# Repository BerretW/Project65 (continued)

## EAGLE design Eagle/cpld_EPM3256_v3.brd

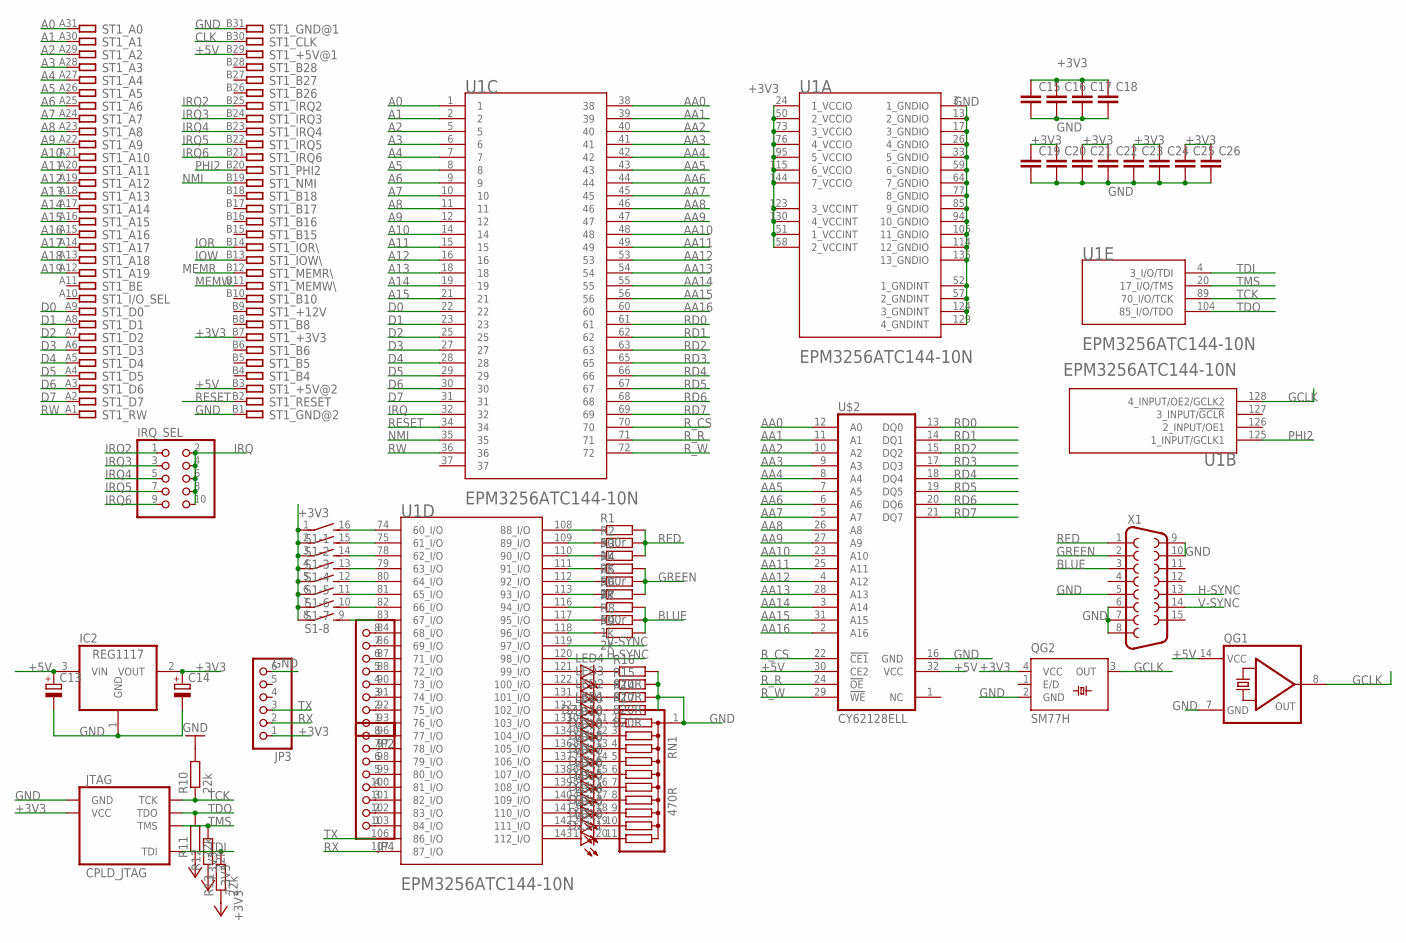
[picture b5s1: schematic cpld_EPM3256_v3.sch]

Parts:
C13, C14: CPOL-EUE2.5-5; E2,5-5
C15, C16, C17, C18, C19, C20, C21, C22, C23, C24, C25, C26: C-EU050-035X075; C050-035X075
DZ1: LB10
IC2: REG1117; SOT223
IRQ_SEL: PINHD-2X5; 2X05
JP2, JP4: PINHD-1X8; 1X08
JP3: PINHD-1X6/90; 1X06/90
JTAG: CPLD_JTAG; 2X05
LED1, LED2, LED3, LED4: LED3MM
QG1: QG5860; DIL14S
QG2: SM77H
R1, R4, R7: 500r; 0204V
R2, R5, R8: 1k; 0204V
R3, R6, R9: 2k; 0204V
R10, R11, R12, R13: 22k; 0207/7
R14, R15, R16, R17: 820R; 0207/2V
RN1: 470R; SIL11
S1: DIP08S
ST1: IBM8BIT_ISA; IBM8BIT
U1: EPM3256ATC144; TQFP144-BB
U$2: CY62128ELL; SOIC32
X1: F15HDH; HDF15H

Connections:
74: S1.16 (2), U1.74 (60_I/O)
75: S1.15 (2), U1.75 (61_I/O)
78: S1.14 (2), U1.78 (62_I/O)
79: S1.13 (2), U1.79 (63_I/O)
80: S1.12 (2), U1.80 (64_I/O)
81: S1.11 (2), U1.81 (65_I/O)
82: S1.10 (2), U1.82 (66_I/O)
83: S1.9 (2), U1.83 (67_I/O)
84: JP2.8, U1.84 (68_I/O)
86: JP2.7, U1.86 (69_I/O)
87: JP2.6, U1.87 (71_I/O)
88: JP2.5, U1.88 (72_I/O)
90: JP2.4, U1.90 (73_I/O)
91: JP2.3, U1.91 (74_I/O)
92: JP2.2, U1.92 (75_I/O)
93: JP2.1, U1.93 (76_I/O)
96: JP4.8, U1.96 (77_I/O)
97: JP4.7, U1.97 (78_I/O)
98: JP4.6, U1.98 (79_I/O)
99: JP4.5, U1.99 (80_I/O)
100: JP4.4, U1.100 (81_I/O)
101: JP4.3, U1.101 (82_I/O)
102: JP4.2, U1.102 (83_I/O)
103: JP4.1, U1.103 (84_I/O)
121: LED4.A, U1.121 (99_I/O)
122: LED3.A, U1.122 (100_I/O)
131: LED2.A, U1.131 (101_I/O)
132: LED1.A, U1.132 (102_I/O)
133: DZ1.10 (A), U1.133 (103_I/O)
134: DZ1.9 (A), U1.134 (104_I/O)
136: DZ1.8 (A), U1.136 (105_I/O)
137: DZ1.7 (A), U1.137 (106_I/O)
138: DZ1.6 (A), U1.138 (107_I/O)
139: DZ1.5 (A), U1.139 (108_I/O)
140: DZ1.4 (A), U1.140 (109_I/O)
141: DZ1.3 (A), U1.141 (110_I/O)
142: DZ1.2 (A), U1.142 (111_I/O)
143: DZ1.1 (A), U1.143 (112_I/O)
+3V3: C14.+, C15.1, C16.1, C17.1, C18.1, C19.1, C20.1, C21.1, C22.1, C23.1, C24.1, C25.1, C26.1, IC2.2 (VOUT), JP3.1, JTAG.4 (VCC), QG2.4 (VCC), R11.1, R12.1, R13.1, S1.1, S1.2 (1), S1.3 (1), S1.4 (1), S1.5 (1), S1.6 (1), S1.7 (1), S1.8 (1), ST1.B7, U1.24 (1_VCCIO), U1.50 (2_VCCIO), U1.51 (1_VCCINT), U1.58 (2_VCCINT), U1.73 (3_VCCIO), U1.76 (4_VCCIO), U1.95 (5_VCCIO), U1.115 (6_VCCIO), U1.123 (3_VCCINT), U1.130 (4_VCCINT), U1.144 (7_VCCIO)
+5V: C13.+, IC2.3 (VIN), QG1.14 (VCC), ST1.B3, ST1.B29, U$2.30 (CE2), U$2.32 (VCC)
A0: ST1.A31, U1.1
A1: ST1.A30, U1.2
A2: ST1.A29, U1.5
A3: ST1.A28, U1.6
A4: ST1.A27, U1.7
A5: ST1.A26, U1.8
A6: ST1.A25, U1.9
A7: ST1.A24, U1.10
A8: ST1.A23, U1.11
A9: ST1.A22, U1.12
A10: ST1.A21, U1.14
A11: ST1.A20, U1.15
A12: ST1.A19, U1.16
A13: ST1.A18, U1.18
A14: ST1.A17, U1.19
A15: ST1.A16, U1.21
A16: ST1.A15
A17: ST1.A14
A18: ST1.A13
A19: ST1.A12
AA0: U1.38, U$2.12 (A0)
AA1: U1.39, U$2.11 (A1)
AA2: U1.40, U$2.10 (A2)
AA3: U1.41, U$2.9 (A3)
AA4: U1.42, U$2.8 (A4)
AA5: U1.43, U$2.7 (A5)
AA6: U1.44, U$2.6 (A6)
AA7: U1.45, U$2.5 (A7)
AA8: U1.46, U$2.26 (A8)
AA9: U1.47, U$2.27 (A9)
AA10: U1.48, U$2.23 (A10)
AA11: U1.49, U$2.25 (A11)
AA12: U1.53, U$2.4 (A12)
AA13: U1.54, U$2.28 (A13)
AA14: U1.55, U$2.3 (A14)
AA15: U1.56, U$2.31 (A15)
AA16: U1.60, U$2.2 (A16)
B1: R8.1, U1.117 (95_I/O)
B2: R9.1, U1.118 (96_I/O)
B5: R7.1, U1.116 (94_I/O)
BLUE: R7.2, R8.2, R9.2, X1.3
CLK: ST1.B30
D0: ST1.A9, U1.22
D1: ST1.A8, U1.23
D2: ST1.A7, U1.25
D3: ST1.A6, U1.27
D4: ST1.A5, U1.28
D5: ST1.A4, U1.29
D6: ST1.A3, U1.30
D7: ST1.A2, U1.31
G1: R5.1, U1.112 (92_I/O)
G2: R6.1, U1.113 (93_I/O)
G5: R4.1, U1.111 (91_I/O)
GCLK: QG1.8 (OUT), QG2.3 (OUT), U1.128 (4_INPUT/OE2/GCLK2)
GND: C13.-, C14.-, C15.2, C16.2, C17.2, C18.2, C19.2, C20.2, C21.2, C22.2, C23.2, C24.2, C25.2, C26.2, IC2.1 (GND), JP3.6, JTAG.2 (GND), JTAG.6 (GND), JTAG.7 (GND), JTAG.8 (GND), JTAG.10 (GND), QG1.7 (GND), QG2.2 (GND), R10.2, R14.2, R15.2, R16.2, R17.2, RN1.1, ST1.B1, ST1.B31, U1.3 (1_GNDIO), U1.13 (2_GNDIO), U1.17 (3_GNDIO), U1.26 (4_GNDIO), U1.33 (5_GNDIO), U1.52 (1_GNDINT), U1.57 (2_GNDINT), U1.59 (6_GNDIO), U1.64 (7_GNDIO), U1.77 (8_GNDIO), U1.85 (9_GNDIO), U1.94 (10_GNDIO), U1.105 (11_GNDIO), U1.114 (12_GNDIO), U1.124 (3_GNDINT), U1.129 (4_GNDINT), U1.135 (13_GNDIO), U$2.16 (GND), X1.5, X1.6, X1.7, X1.8, X1.9, X1.10
GREEN: R4.2, R5.2, R6.2, X1.2
H-SYNC: U1.120 (98_I/O), X1.13
IOR: ST1.B14
IOW: ST1.B13
IRQ: IRQ_SEL.2, IRQ_SEL.4, IRQ_SEL.6, IRQ_SEL.8, IRQ_SEL.10, U1.32
IRQ2: IRQ_SEL.1, ST1.B25
IRQ3: IRQ_SEL.3, ST1.B24
IRQ4: IRQ_SEL.5, ST1.B23
IRQ5: IRQ_SEL.7, ST1.B22
IRQ6: IRQ_SEL.9, ST1.B21
MEMR: ST1.B12
MEMW: ST1.B11
unnamed: LED2.K (C), R14.1
unnamed: LED3.K (C), R15.1
unnamed: LED4.K (C), R16.1
unnamed: LED1.K (C), R17.1
unnamed: DZ1.20 (C), RN1.11
unnamed: DZ1.19 (C), RN1.10
unnamed: DZ1.18 (C), RN1.9
unnamed: DZ1.17 (C), RN1.8
unnamed: DZ1.16 (C), RN1.7
unnamed: DZ1.15 (C), RN1.6
unnamed: DZ1.14 (C), RN1.5
unnamed: DZ1.13 (C), RN1.4
unnamed: DZ1.12 (C), RN1.3
unnamed: DZ1.11 (C), RN1.2
NMI: ST1.B19, U1.35
PHI2: ST1.B20, U1.125 (1_INPUT/GCLK1)
R1: R2.1, U1.109 (89_I/O)
R2: R3.1, U1.110 (90_I/O)
R5: R1.1, U1.108 (88_I/O)
RD0: U1.61, U$2.13 (DQ0)
RD1: U1.62, U$2.14 (DQ1)
RD2: U1.63, U$2.15 (DQ2)
RD3: U1.65, U$2.17 (DQ3)
RD4: U1.66, U$2.18 (DQ4)
RD5: U1.67, U$2.19 (DQ5)
RD6: U1.68, U$2.20 (DQ6)
RD7: U1.69, U$2.21 (DQ7)
RED: R1.2, R2.2, R3.2, X1.1
RESET: ST1.B2, U1.34
RW: ST1.A1, U1.36
RX: JP3.2, U1.107 (87_I/O)
R_CS: U1.70, U$2.22 (!CE1)
R_R: U1.71, U$2.24 (!OE)
R_W: U1.72, U$2.29 (!WE)
TCK: JTAG.1 (TCK), R10.1, U1.89 (70_I/O/TCK)
TDI: JTAG.9 (TDI), R13.2, U1.4 (3_I/O/TDI)
TDO: JTAG.3 (TDO), R11.2, U1.104 (85_I/O/TDO)
TMS: JTAG.5 (TMS), R12.2, U1.20 (17_I/O/TMS)
TX: JP3.3, U1.106 (86_I/O)
V-SYNC: U1.119 (97_I/O), X1.14

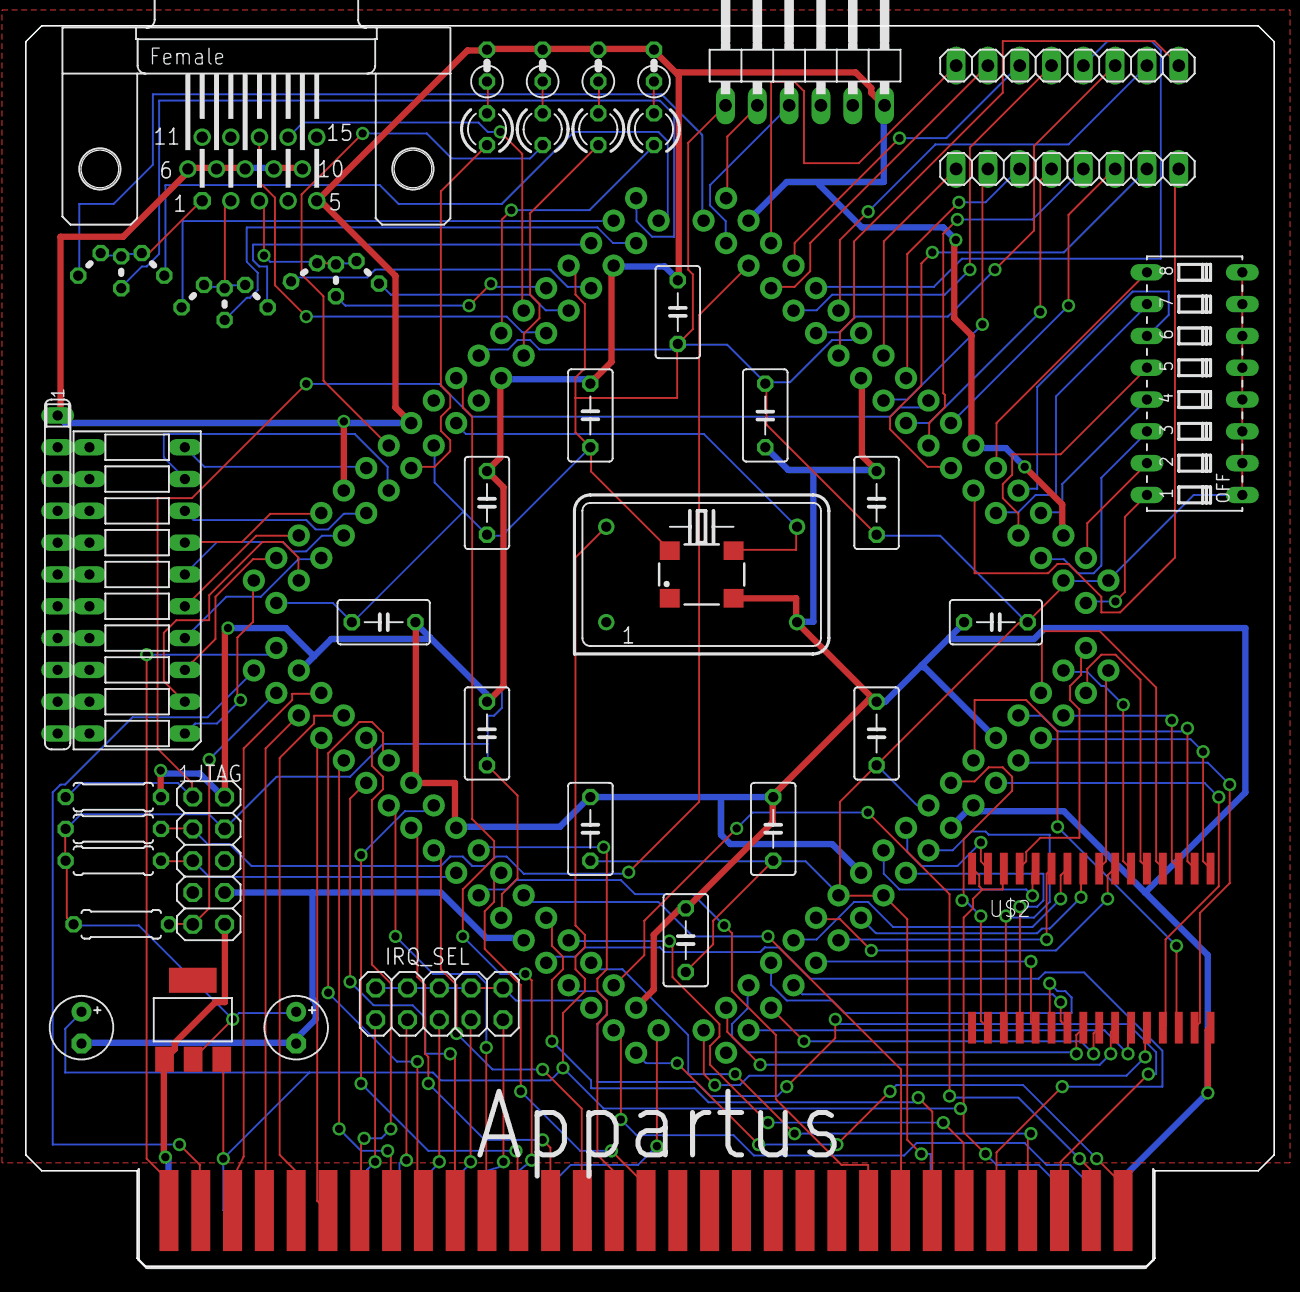
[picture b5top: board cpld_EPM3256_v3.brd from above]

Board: 2 copper layers, 99.7 x 99.1 mm, 50 parts (0 on the bottom side), 138 nets.

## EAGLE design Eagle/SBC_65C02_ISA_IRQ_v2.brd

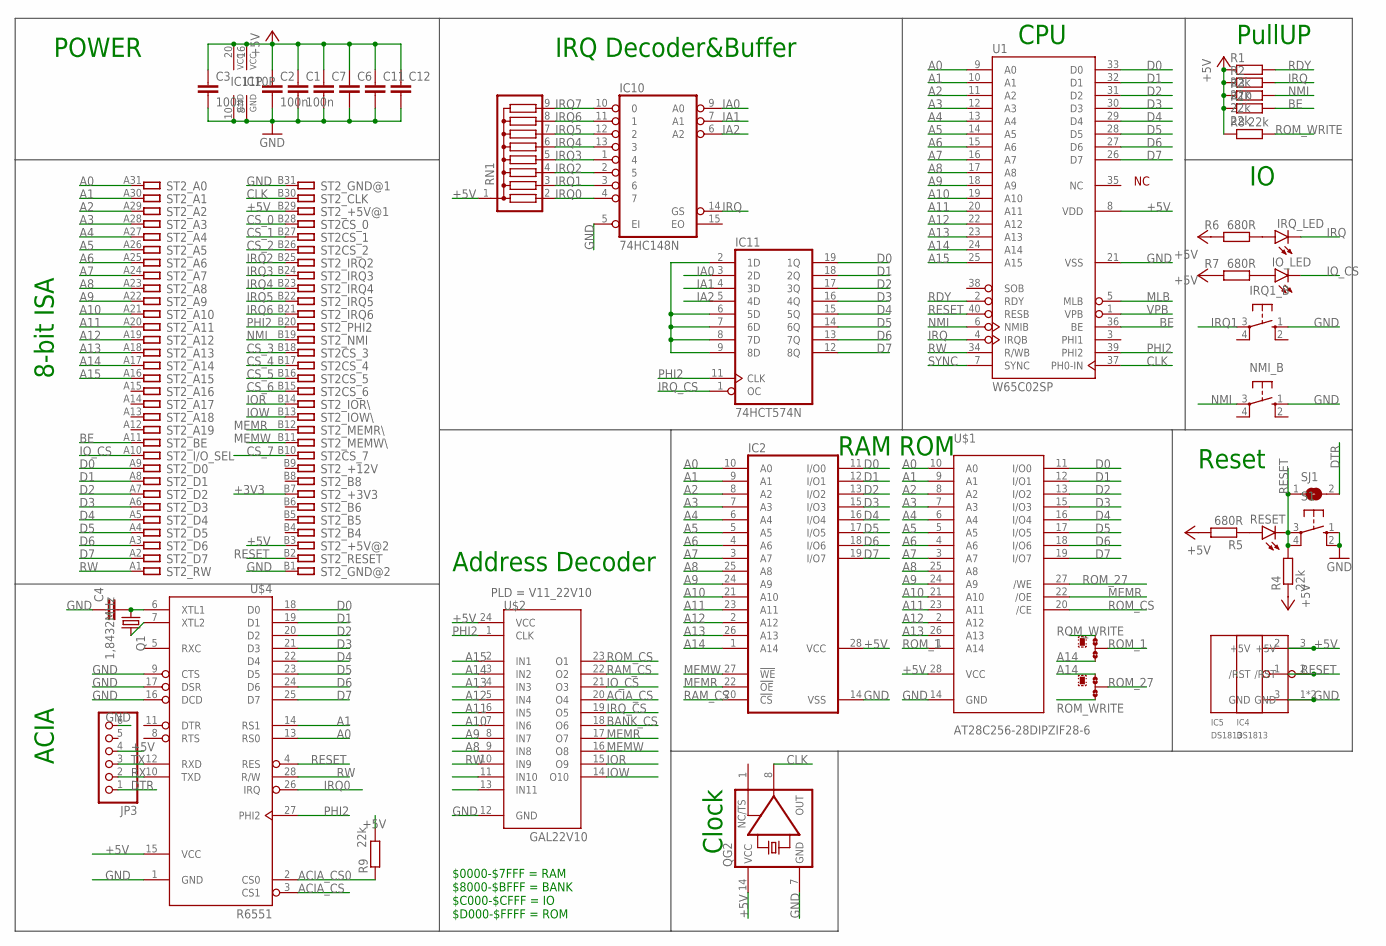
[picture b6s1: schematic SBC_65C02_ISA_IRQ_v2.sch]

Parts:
C1, C2, C3: 100n; C050-025X075
C4: C-EU025-030X050; C025-030X050
C6, C7, C11, C12: C-EU050-035X075; C050-035X075
IC2: 62256P; DIL28-6
IC4: DS1813; SOT223
IC5: DS1813; TO-92
IC10: 74HC148N; DIL16
IC11: 74HCT574N; DIL20
IO_LED: LED5MM
IRQ1_B: 10-XX; B3F-10XX
IRQ_LED: LED5MM
JP3: PINHD-1X6/90; 1X06/90
NMI_B: 10-XX; B3F-10XX
Q1: 1,8432MHz; HC49/S
QG2: XO-14; DIL14S
R1, R2, R3, R4, R8, R9, R10: 22k; 0207/10
R5, R6, R7: 680R; 0207/10
RESET: LED5MM
RN1: G08R; SIL9
ROM_1, ROM_27: 0R-JUMPA; A0R-JMP
S1: 10-XX; B3F-10XX
SJ1: SJ
ST2: IBM8BIT_ISASHORT; APP_2X32_SHORT
U1: W65C02SP; DIP-40
U$1: AT28C256-28DIPZIF28-6; 228-1277-00-0602J
U$2: GAL22V10; DIL28_1
U$4: R6551; DIP-28

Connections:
+3V3: ST2.B7
+5V: C1.1, C2.1, C3.1, C6.1, C7.1, C11.1, C12.1, IC2.28 (VCC), IC4.3 (+5V), IC5.2 (+5V), IC10.16 (VCC), IC11.20 (VCC), JP3.4, QG2.14 (VCC), R1.1, R2.1, R3.1, R4.1, R5.2, R6.2, R7.2, R8.1, R9.2, R10.1, RN1.1, ST2.B3, ST2.B29, U1.8 (VDD), U$1.28 (VCC), U$2.24 (VCC), U$4.15 (VCC)
A0: IC2.10 (A0), ST2.A31, U1.9 (A0), U$1.10 (A0), U$4.13 (RS0)
A1: IC2.9 (A1), ST2.A30, U1.10 (A1), U$1.9 (A1), U$4.14 (RS1)
A2: IC2.8 (A2), ST2.A29, U1.11 (A2), U$1.8 (A2)
A3: IC2.7 (A3), ST2.A28, U1.12 (A3), U$1.7 (A3)
A4: IC2.6 (A4), ST2.A27, U1.13 (A4), U$1.6 (A4)
A5: IC2.5 (A5), ST2.A26, U1.14 (A5), U$1.5 (A5)
A6: IC2.4 (A6), ST2.A25, U1.15 (A6), U$1.4 (A6)
A7: IC2.3 (A7), ST2.A24, U1.16 (A7), U$1.3 (A7)
A8: IC2.25 (A8), ST2.A23, U1.17 (A8), U$1.25 (A8), U$2.9 (IN8)
A9: IC2.24 (A9), ST2.A22, U1.18 (A9), U$1.24 (A9), U$2.8 (IN7)
A10: IC2.21 (A10), ST2.A21, U1.19 (A10), U$1.21 (A10), U$2.7 (IN6)
A11: IC2.23 (A11), ST2.A20, U1.20 (A11), U$1.23 (A11), U$2.6 (IN5)
A12: IC2.2 (A12), ST2.A19, U1.22 (A12), U$1.2 (A12), U$2.5 (IN4)
A13: IC2.26 (A13), ST2.A18, U1.23 (A13), U$1.26 (A13), U$2.4 (IN3)
A14: IC2.1 (A14), ROM_1.3, ROM_27.1, ST2.A17, U1.24 (A14), U$2.3 (IN2)
A15: ST2.A16, U1.25 (A15), U$2.2 (IN1)
ACIA_CS: U$2.20 (O4), U$4.3 (CS1)
ACIA_CS0: R9.1, U$4.2 (CS0)
BANK_CS: U$2.18 (O6)
BE: R10.2, ST2.A11, U1.36 (BE)
CLK: QG2.8 (OUT), ST2.B30, U1.37 (PH0-IN)
CS_0: ST2.B28
CS_1: ST2.B27
CS_2: ST2.B26
CS_3: ST2.B18
CS_4: ST2.B17
CS_5: ST2.B16
CS_6: ST2.B15
CS_7: ST2.B10
D0: IC2.11 (I/O0), IC11.19 (1Q), ST2.A9, U1.33 (D0), U$1.11 (I/O0), U$4.18 (D0)
D1: IC2.12 (I/O1), IC11.18 (2Q), ST2.A8, U1.32 (D1), U$1.12 (I/O1), U$4.19 (D1)
D2: IC2.13 (I/O2), IC11.17 (3Q), ST2.A7, U1.31 (D2), U$1.13 (I/O2), U$4.20 (D2)
D3: IC2.15 (I/O3), IC11.16 (4Q), ST2.A6, U1.30 (D3), U$1.15 (I/O3), U$4.21 (D3)
D4: IC2.16 (I/O4), IC11.15 (5Q), ST2.A5, U1.29 (D4), U$1.16 (I/O4), U$4.22 (D4)
D5: IC2.17 (I/O5), IC11.14 (6Q), ST2.A4, U1.28 (D5), U$1.17 (I/O5), U$4.23 (D5)
D6: IC2.18 (I/O6), IC11.13 (7Q), ST2.A3, U1.27 (D6), U$1.18 (I/O6), U$4.24 (D6)
D7: IC2.19 (I/O7), IC11.12 (8Q), ST2.A2, U1.26 (D7), U$1.19 (I/O7), U$4.25 (D7)
DTR: JP3.1, SJ1.2
GND: C1.2, C2.2, C3.2, C4.1, C6.2, C7.2, C11.2, C12.2, IC2.14 (VSS), IC4.1 (GND), IC4.4 (GND), IC5.3 (GND), IC10.5 (EI), IC10.8 (GND), IC11.10 (GND), IRQ1_B.1 (S), JP3.6, NMI_B.1 (S), QG2.7 (GND), S1.1 (S), S1.2 (S1), ST2.B1, ST2.B31, U1.21 (VSS), U$1.14 (GND), U$2.12 (GND), U$4.1 (GND), U$4.9 (CTS), U$4.16 (DCD), U$4.17 (DSR)
IA0: IC10.9 (A0), IC11.3 (2D)
IA1: IC10.7 (A1), IC11.4 (3D)
IA2: IC10.6 (A2), IC11.5 (4D)
IOR: ST2.B14, U$2.15 (O9)
IOW: ST2.B13, U$2.14 (O10)
IO_CS: IO_LED.K (C), ST2.A10, U$2.21 (O3)
IRQ: IC10.14 (GS), IRQ_LED.K (C), R2.2, U1.4 (IRQB)
IRQ0: IC10.4 (7), RN1.2, U$4.26 (IRQ)
IRQ1: IC10.3 (6), IRQ1_B.3, RN1.3
IRQ2: IC10.2 (5), RN1.4, ST2.B25
IRQ3: IC10.1 (4), RN1.5, ST2.B24
IRQ4: IC10.13 (3), RN1.6, ST2.B23
IRQ5: IC10.12 (2), RN1.7, ST2.B22
IRQ6: IC10.11 (1), RN1.8, ST2.B21
IRQ7: IC10.10 (0), RN1.9
IRQ_CS: IC11.1 (OC), U$2.19 (O5)
MEMR: IC2.22 (!OE), ST2.B12, U$1.22 (/OE), U$2.17 (O7)
MEMW: IC2.27 (!WE), ST2.B11, U$2.16 (O8)
MLB: U1.5 (MLB)
unnamed: IRQ_LED.A, R6.1
unnamed: R5.1, RESET.A
unnamed: IO_LED.A, R7.1
unnamed: IC11.2 (1D), IC11.6 (5D), IC11.7 (6D), IC11.8 (7D), IC11.9 (8D)
unnamed: C4.2, Q1.1, U$4.6 (XTL1)
unnamed: Q1.2, U$4.7 (XTL2)
NMI: NMI_B.3, R3.2, ST2.B19, U1.6 (NMIB)
PHI2: IC11.11 (CLK), ST2.B20, U1.39 (PHI2), U$2.1 (CLK), U$4.27 (PHI2)
RAM_CS: IC2.20 (!CS), U$2.22 (O2)
RDY: R1.2, U1.2 (RDY)
RESET: IC4.2 (/RST), IC5.1 (/RST), R4.2, RESET.K (C), S1.3, S1.4 (P1), SJ1.1, ST2.B2, U1.40 (RESB), U$4.4 (RES)
ROM_1: ROM_1.2, U$1.1 (A14)
ROM_27: ROM_27.2, U$1.27 (/WE)
ROM_CS: U$1.20 (/CE), U$2.23 (O1)
ROM_WRITE: R8.2, ROM_1.1, ROM_27.3
RW: ST2.A1, U1.34 (R/WB), U$2.10 (IN9), U$4.28 (R/W)
RX: JP3.2, U$4.10 (TXD)
SYNC: U1.7 (SYNC)
TX: JP3.3, U$4.12 (RXD)
VPB: U1.1 (VPB)

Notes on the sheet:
$0000-$7FFF = RAM $8000-$BFFF = BANK $C000-$CFFF = IO $D000-$FFFF = ROM
ACIA
Address Decoder
Reset
CPU
POWER
8-bit ISA
RAM ROM
Clock
PullUP
PLD = V11_22V10
IRQ Decoder&Buffer

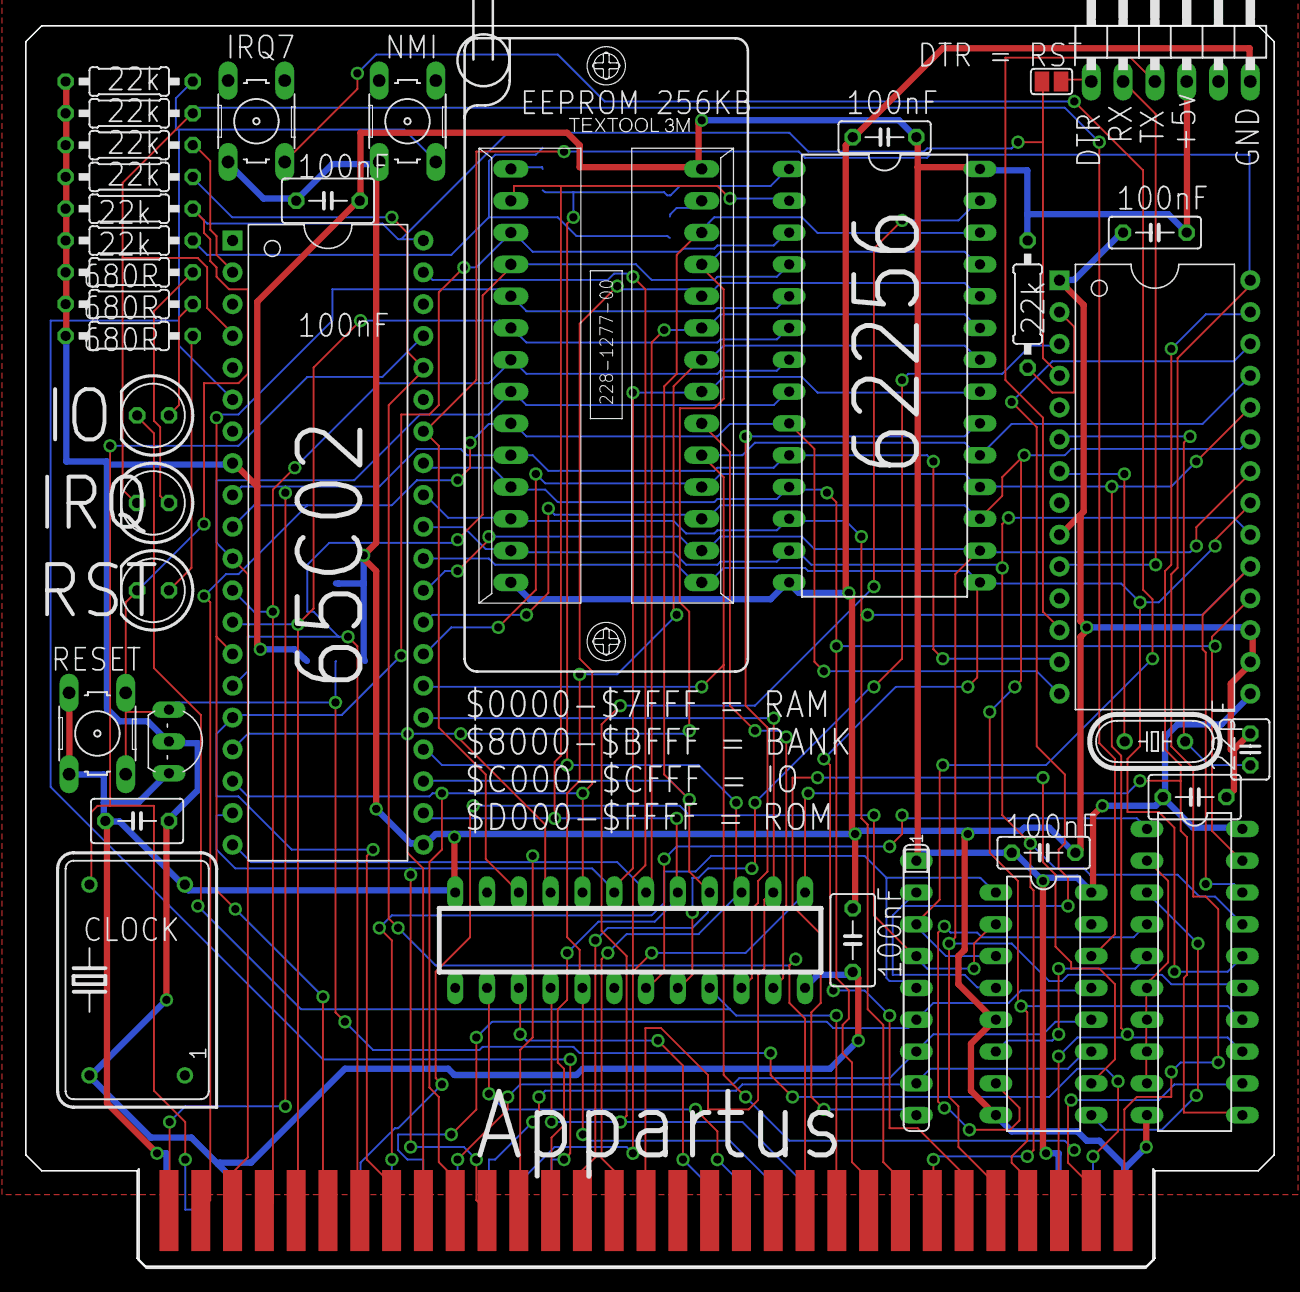
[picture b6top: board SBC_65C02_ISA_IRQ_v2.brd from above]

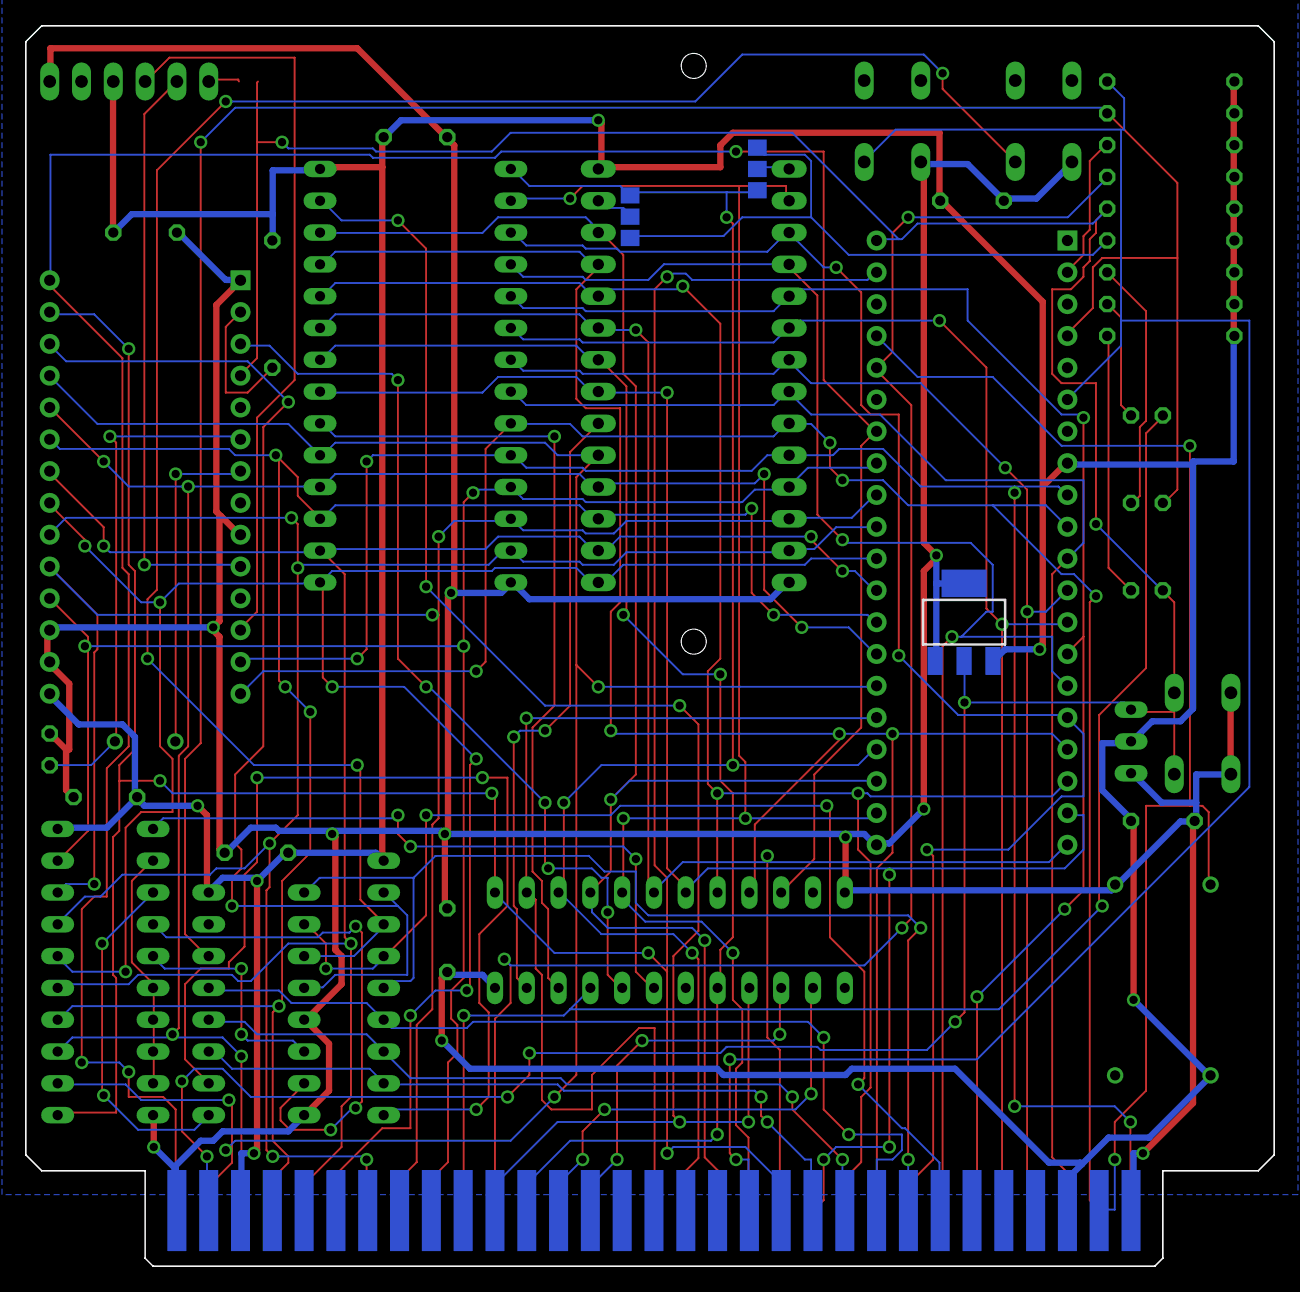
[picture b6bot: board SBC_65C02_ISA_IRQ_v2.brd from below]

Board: 2 copper layers, 99.7 x 99.1 mm, 41 parts (3 on the bottom side), 67 nets.

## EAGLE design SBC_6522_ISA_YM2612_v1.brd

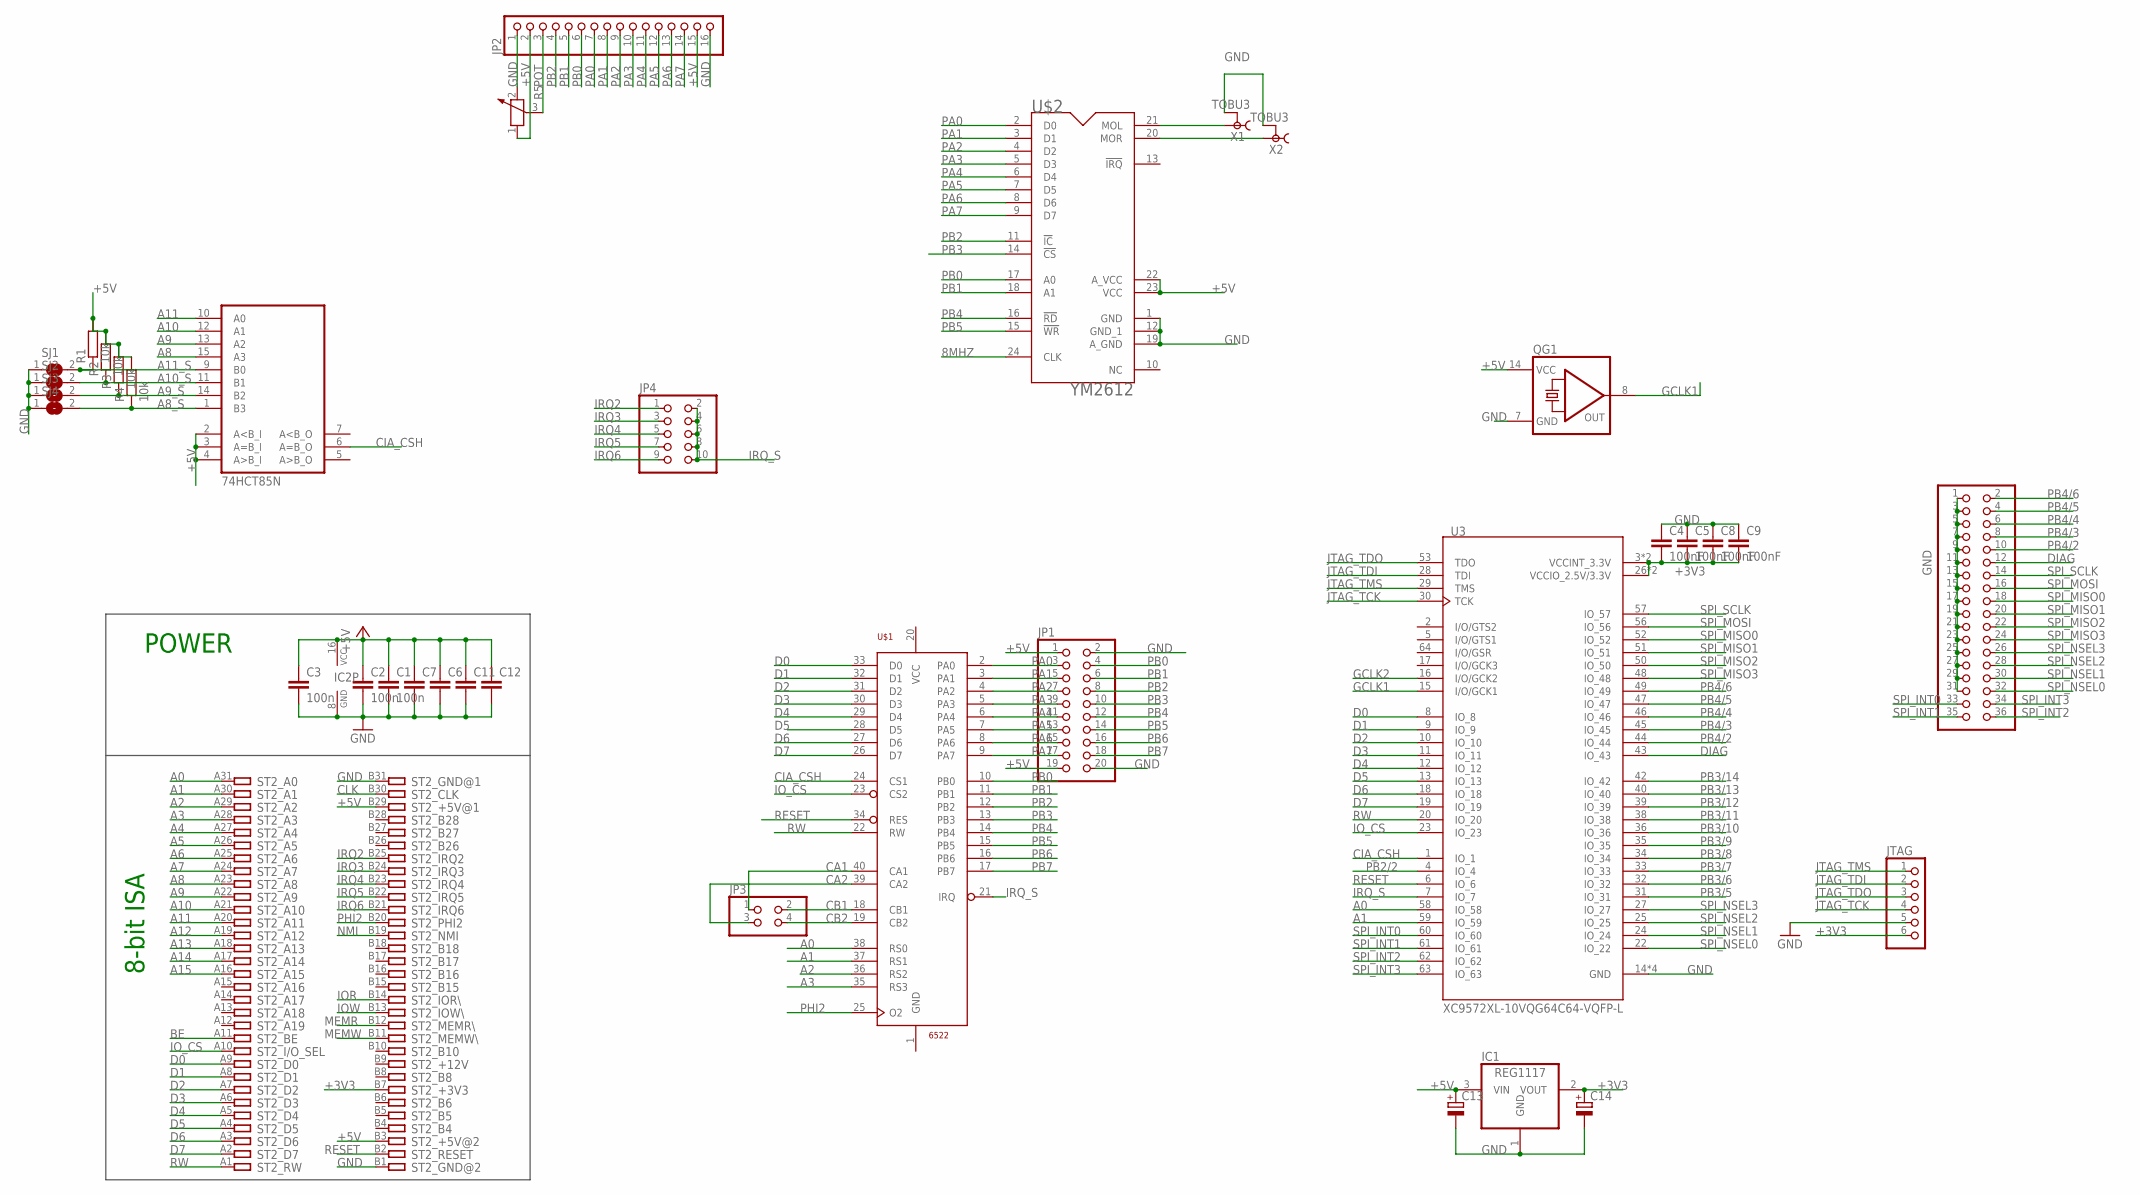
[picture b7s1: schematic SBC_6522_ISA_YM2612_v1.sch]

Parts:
C1, C2, C3: 100n; C050-025X075
C4, C5, C8, C9: 100nF; C603
C6, C7, C11, C12: C-EU050-035X075; C050-035X075
C13, C14: CPOL-EUE2.5-5; E2,5-5
IC1: REG1117; SOT223
IC2: 74HCT85N; DIL16
JP1: PINHD-2X10; 2X10
JP2: PINHD-1X16; 1X16
JP3: PINHD-2X2; 2X02
JP4: PINHD-2X5; 2X05
JP5: PINHD-2X18; 2X18
JTAG: PINHD-1X6; 1X06
QG1: QG5860; DIL14S
R1, R2, R3, R4: 10k; 0207/7
R5: POTENTIOMETER_PT-10; PT-10
SJ1, SJ2, SJ3, SJ4: SJ
ST2: IBM8BIT_ISASHORT; APP_2X32_SHORT
U3: XC9572XL-10VQG64C64-VQFP-L; VQFP64
U$1: 6522
U$2: YM2612; DIL24
X1, X2: TOBU3

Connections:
8MHZ: U$2.24 (CLK)
+3V3: C4.2, C5.2, C8.2, C9.2, C14.+, IC1.2 (VOUT), JTAG.6, ST2.B7, U3.3 (VCCINT_3.3V), U3.26 (VCCIO_2.5V/3.3V), U3.37 (VCCINT_3.3V), U3.55 (VCCIO_2.5V/3.3V)
+5V: C1.1, C2.1, C3.1, C6.1, C7.1, C11.1, C12.1, C13.+, IC1.3 (VIN), IC2.2 (A<B_I), IC2.3 (A=B_I), IC2.4 (A>B_I), IC2.16 (VCC), JP1.1, JP1.19, JP2.2, JP2.15, QG1.14 (VCC), R1.2, R2.2, R3.2, R4.2, R5.1, ST2.B3, ST2.B29, U$2.22 (A_VCC), U$2.23 (VCC)
A0: ST2.A31, U3.58 (IO_58), U$1.38 (RS0)
A1: ST2.A30, U3.59 (IO_59), U$1.37 (RS1)
A2: ST2.A29, U$1.36 (RS2)
A3: ST2.A28, U$1.35 (RS3)
A4: ST2.A27
A5: ST2.A26
A6: ST2.A25
A7: ST2.A24
A8: IC2.15 (A3), ST2.A23
A8_S: IC2.1 (B3), R4.1, SJ4.2
A9: IC2.13 (A2), ST2.A22
A9_S: IC2.14 (B2), R3.1, SJ3.2
A10: IC2.12 (A1), ST2.A21
A10_S: IC2.11 (B1), R2.1, SJ2.2
A11: IC2.10 (A0), ST2.A20
A11_S: IC2.9 (B0), R1.1, SJ1.2
A12: ST2.A19
A13: ST2.A18
A14: ST2.A17
A15: ST2.A16
BE: ST2.A11
CA1: JP3.1, U$1.40 (CA1)
CA2: JP3.3, U$1.39 (CA2)
CB1: JP3.2, U$1.18 (CB1)
CB2: JP3.4, U$1.19 (CB2)
CIA_CSH: IC2.6 (A=B_O), U3.1 (IO_1), U$1.24 (CS1)
CLK: ST2.B30
D0: ST2.A9, U3.8 (IO_8), U$1.33 (D0)
D1: ST2.A8, U3.9 (IO_9), U$1.32 (D1)
D2: ST2.A7, U3.10 (IO_10), U$1.31 (D2)
D3: ST2.A6, U3.11 (IO_11), U$1.30 (D3)
D4: ST2.A5, U3.12 (IO_12), U$1.29 (D4)
D5: ST2.A4, U3.13 (IO_13), U$1.28 (D5)
D6: ST2.A3, U3.18 (IO_18), U$1.27 (D6)
D7: ST2.A2, U3.19 (IO_19), U$1.26 (D7)
DIAG: JP5.12, U3.43 (IO_43)
GCLK1: QG1.8 (OUT), U3.15 (I/O/GCK1)
GCLK2: U3.16 (I/O/GCK2)
GND: C1.2, C2.2, C3.2, C4.1, C5.1, C6.2, C7.2, C8.1, C9.1, C11.2, C12.2, C13.-, C14.-, IC1.1 (GND), IC2.8 (GND), JP1.2, JP1.20, JP2.1, JP2.16, JP5.1, JP5.3, JP5.5, JP5.7, JP5.9, JP5.11, JP5.13, JP5.15, JP5.17, JP5.19, JP5.21, JP5.23, JP5.25, JP5.27, JP5.29, JP5.31, JTAG.5, QG1.7 (GND), R5.2, SJ1.1, SJ2.1, SJ3.1, SJ4.1, ST2.B1, ST2.B31, U3.14 (GND), U3.21 (GND), U3.41 (GND), U3.54 (GND), U$2.1 (GND), U$2.12 (GND_1), U$2.19 (A_GND), X1.2, X1.2@1 (2), X1.2@2 (2), X2.2, X2.2@1 (2), X2.2@2 (2)
IOR: ST2.B14
IOW: ST2.B13
IO_CS: ST2.A10, U3.23 (IO_23), U$1.23 (CS2)
IRQ2: JP4.1, ST2.B25
IRQ3: JP4.3, ST2.B24
IRQ4: JP4.5, ST2.B23
IRQ5: JP4.7, ST2.B22
IRQ6: JP4.9, ST2.B21
IRQ_S: JP4.2, JP4.4, JP4.6, JP4.8, JP4.10, U3.7 (IO_7), U$1.21 (IRQ)
JTAG_TCK: JTAG.4, U3.30 (TCK)
JTAG_TDI: JTAG.2, U3.28 (TDI)
JTAG_TDO: JTAG.3, U3.53 (TDO)
JTAG_TMS: JTAG.1, U3.29 (TMS)
MEMR: ST2.B12
MEMW: ST2.B11
unnamed: U$2.21 (MOL), X1.1
unnamed: U$2.20 (MOR), X2.1
NMI: ST2.B19
PA0: JP1.3, JP2.7, U$1.2 (PA0), U$2.2 (D0)
PA1: JP1.5, JP2.8, U$1.3 (PA1), U$2.3 (D1)
PA2: JP1.7, JP2.9, U$1.4 (PA2), U$2.4 (D2)
PA3: JP1.9, JP2.10, U$1.5 (PA3), U$2.5 (D3)
PA4: JP1.11, JP2.11, U$1.6 (PA4), U$2.6 (D4)
PA5: JP1.13, JP2.12, U$1.7 (PA5), U$2.7 (D5)
PA6: JP1.15, JP2.13, U$1.8 (PA6), U$2.8 (D6)
PA7: JP1.17, JP2.14, U$1.9 (PA7), U$2.9 (D7)
PB0: JP1.4, JP2.6, U$1.10 (PB0), U$2.17 (A0)
PB1: JP1.6, JP2.5, U$1.11 (PB1), U$2.18 (A1)
PB2: JP1.8, JP2.4, U$1.12 (PB2), U$2.11 (!IC)
PB2/2: U3.4 (IO_4)
PB3: JP1.10, U$1.13 (PB3), U$2.14 (!CS)
PB3/5: U3.31 (IO_31)
PB3/6: U3.32 (IO_32)
PB3/7: U3.33 (IO_33)
PB3/8: U3.34 (IO_34)
PB3/9: U3.35 (IO_35)
PB3/10: U3.36 (IO_36)
PB3/11: U3.38 (IO_38)
PB3/12: U3.39 (IO_39)
PB3/13: U3.40 (IO_40)
PB3/14: U3.42 (IO_42)
PB4: JP1.12, U$1.14 (PB4), U$2.16 (!RD)
PB4/2: JP5.10, U3.44 (IO_44)
PB4/3: JP5.8, U3.45 (IO_45)
PB4/4: JP5.6, U3.46 (IO_46)
PB4/5: JP5.4, U3.47 (IO_47)
PB4/6: JP5.2, U3.49 (IO_49)
PB5: JP1.14, U$1.15 (PB5), U$2.15 (!WR)
PB6: JP1.16, U$1.16 (PB6)
PB7: JP1.18, U$1.17 (PB7)
PHI2: ST2.B20, U$1.25 (O2)
POT: JP2.3, R5.3
RESET: ST2.B2, U3.6 (IO_6), U$1.34 (RES)
RW: ST2.A1, U3.20 (IO_20), U$1.22 (RW)
SPI_INT0: JP5.33, U3.60 (IO_60)
SPI_INT1: JP5.35, U3.61 (IO_61)
SPI_INT2: JP5.36, U3.62 (IO_62)
SPI_INT3: JP5.34, U3.63 (IO_63)
SPI_MISO0: JP5.18, U3.52 (IO_52)
SPI_MISO1: JP5.20, U3.51 (IO_51)
SPI_MISO2: JP5.22, U3.50 (IO_50)
SPI_MISO3: JP5.24, U3.48 (IO_48)
SPI_MOSI: JP5.16, U3.56 (IO_56)
SPI_NSEL0: JP5.32, U3.22 (IO_22)
SPI_NSEL1: JP5.30, U3.24 (IO_24)
SPI_NSEL2: JP5.28, U3.25 (IO_25)
SPI_NSEL3: JP5.26, U3.27 (IO_27)
SPI_SCLK: JP5.14, U3.57 (IO_57)

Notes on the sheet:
POWER
8-bit ISA

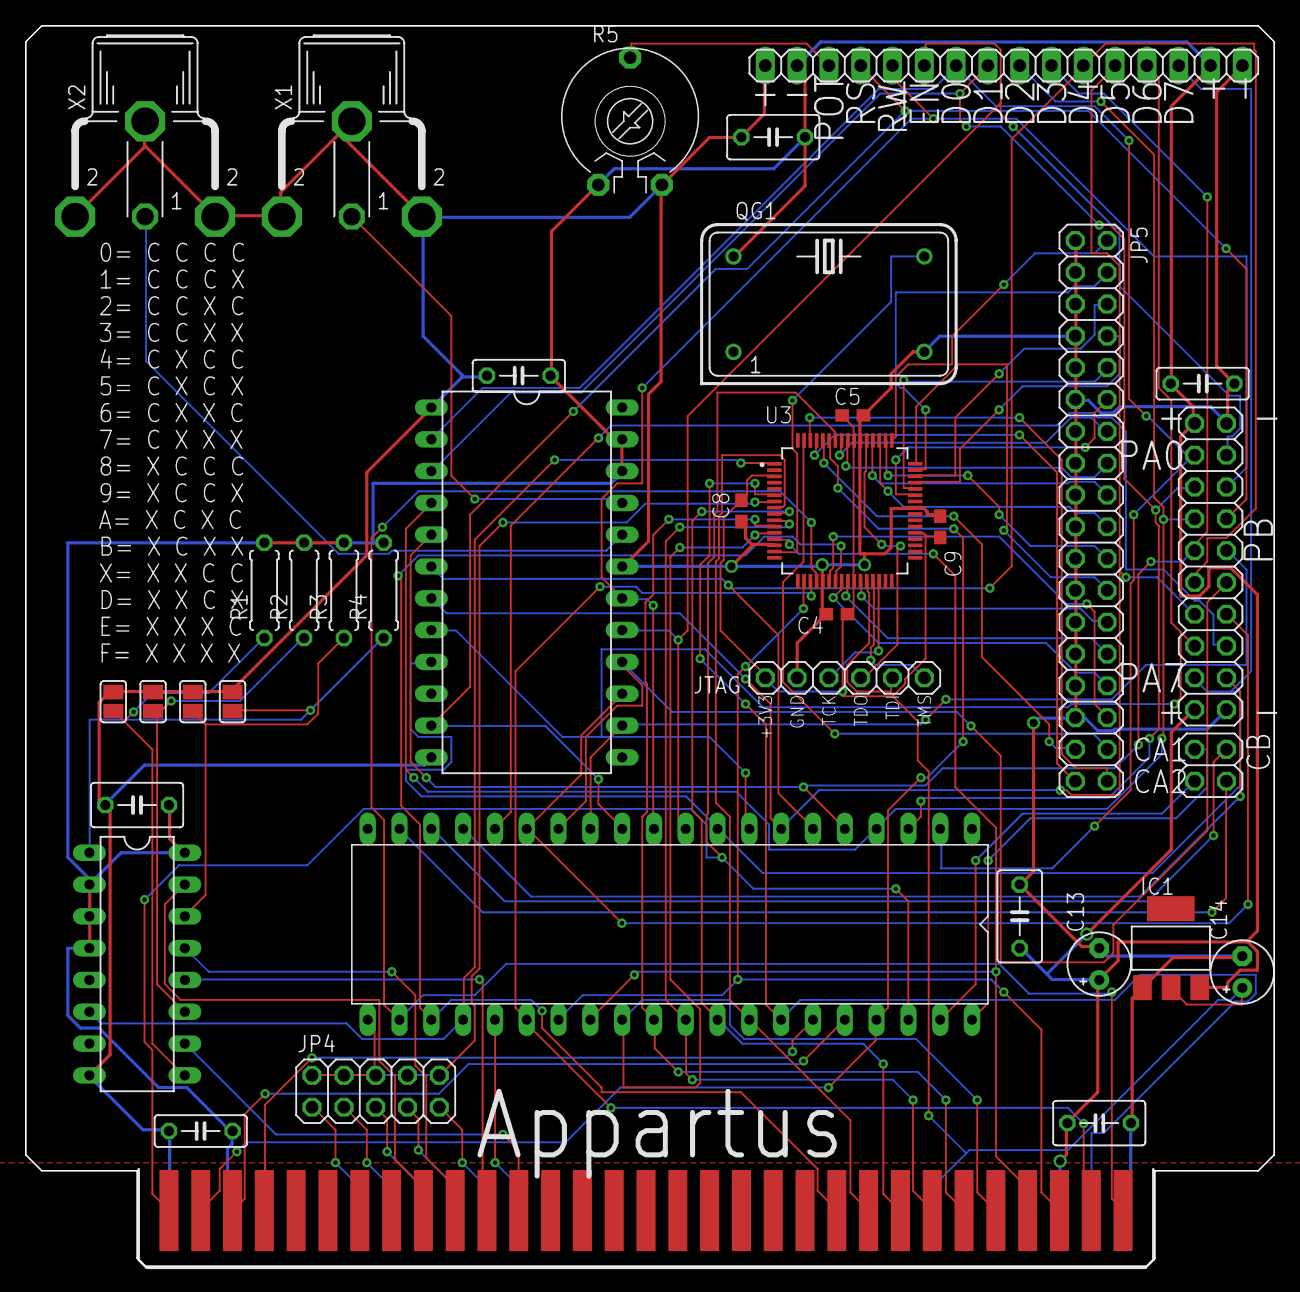
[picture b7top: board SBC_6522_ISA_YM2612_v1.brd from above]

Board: 2 copper layers, 99.7 x 99.1 mm, 37 parts (0 on the bottom side), 82 nets.
